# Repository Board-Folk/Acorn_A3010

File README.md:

# Reproduction A3010 PCB #

This repository contains the schematics and PCB layout for a reproduction
of the Acorn A3010 computer PCB - specifically the 194,003 issue 1.

Other variations of the board exist and may be included as separate designs
at a future date.

Where possible the board matches the location of components and routing of
traces.

## Progress ##

The schematics and PCB design are both complete. An initial fabrication run has
been completed and in the process of being tested. The first board is populated
and while it appears to be working over the post port, there is no apparent video
output

### Changes from first test build ###

The AC inputs to the Mean Well psu were reversed. This should not technically
Be a problem for the psi so can be considered cosmetic.

Footprint pad sizes have been enlarged for the LQFP and J-leg components to aid
With hand assembly.

### Known issues ###

The specified fuse rating for the AC input is inadequate for the Mean Well psu.
The initial power-up produces a spike in current that blows the fuse immediately,
it may prove more appropriate to remove the fuse and add protection to the outputs 

## Factory Fixes ##

The original boards include a number of fixes, these have been incorporated
into the design where possible.

## Variations From Standard ##

In a few places the board is non-standard to allow the use of modern, available
components, most notably the power supply area of the board. Instead of the 
original circuits the board is designed to accept a Mean Well unit that is 
both lighter and more efficient.

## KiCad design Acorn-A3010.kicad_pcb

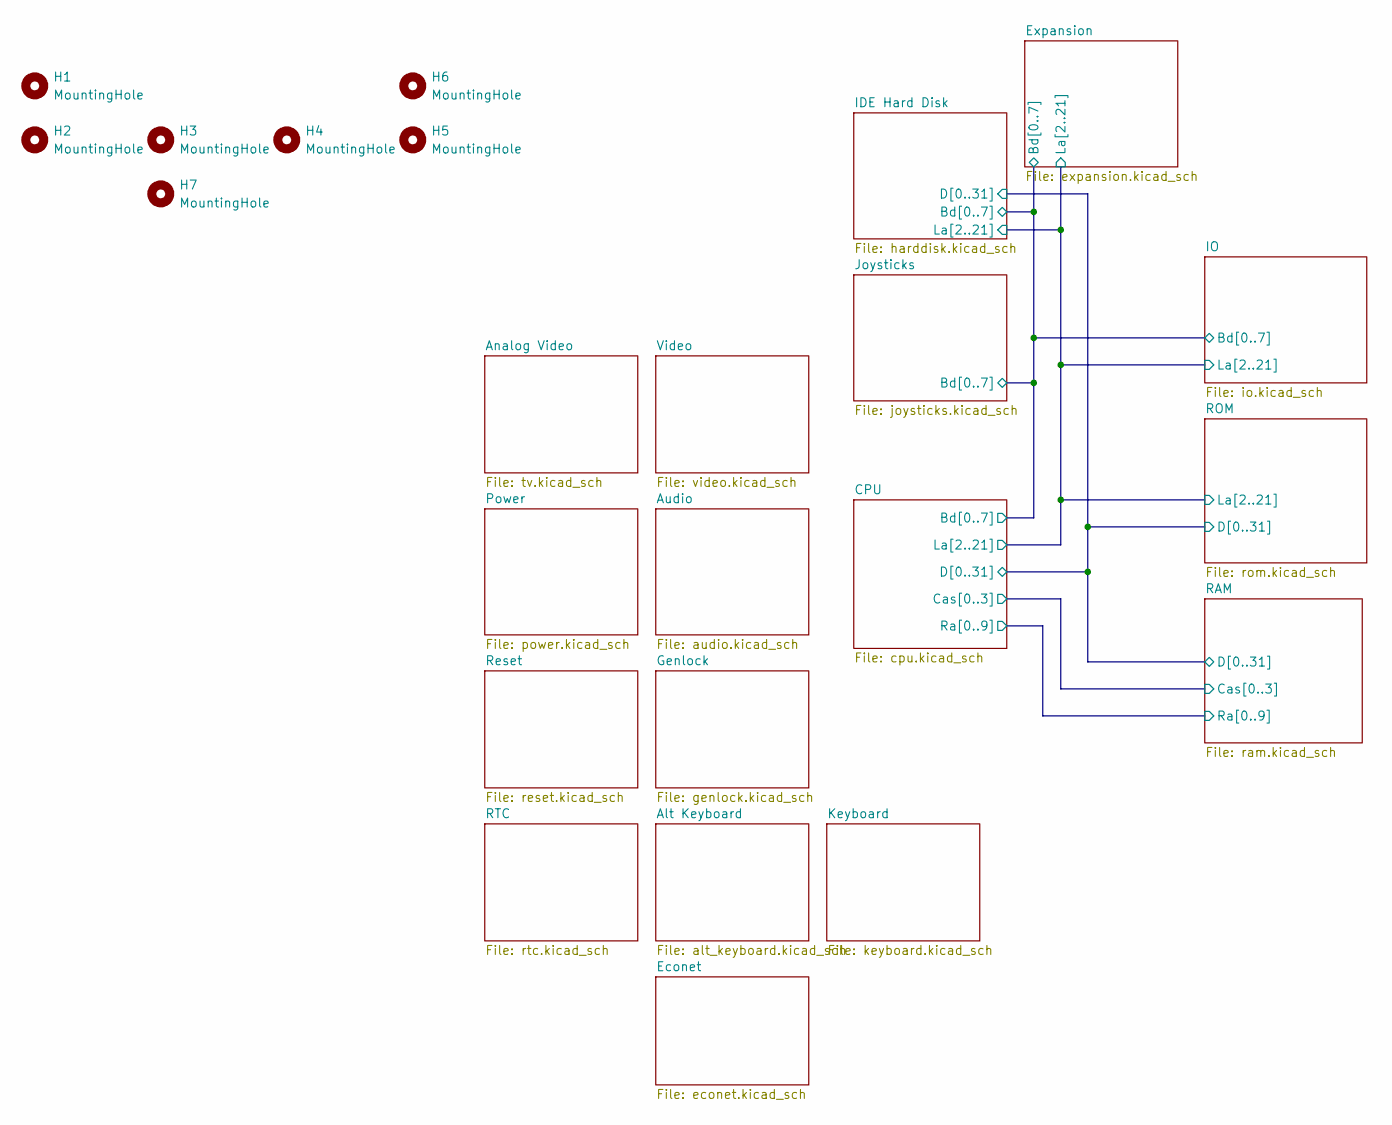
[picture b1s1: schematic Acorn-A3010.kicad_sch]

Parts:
H1, H2, H3, H4, H5, H6, H7: MountingHole; MountingHole_3.2mm_M3

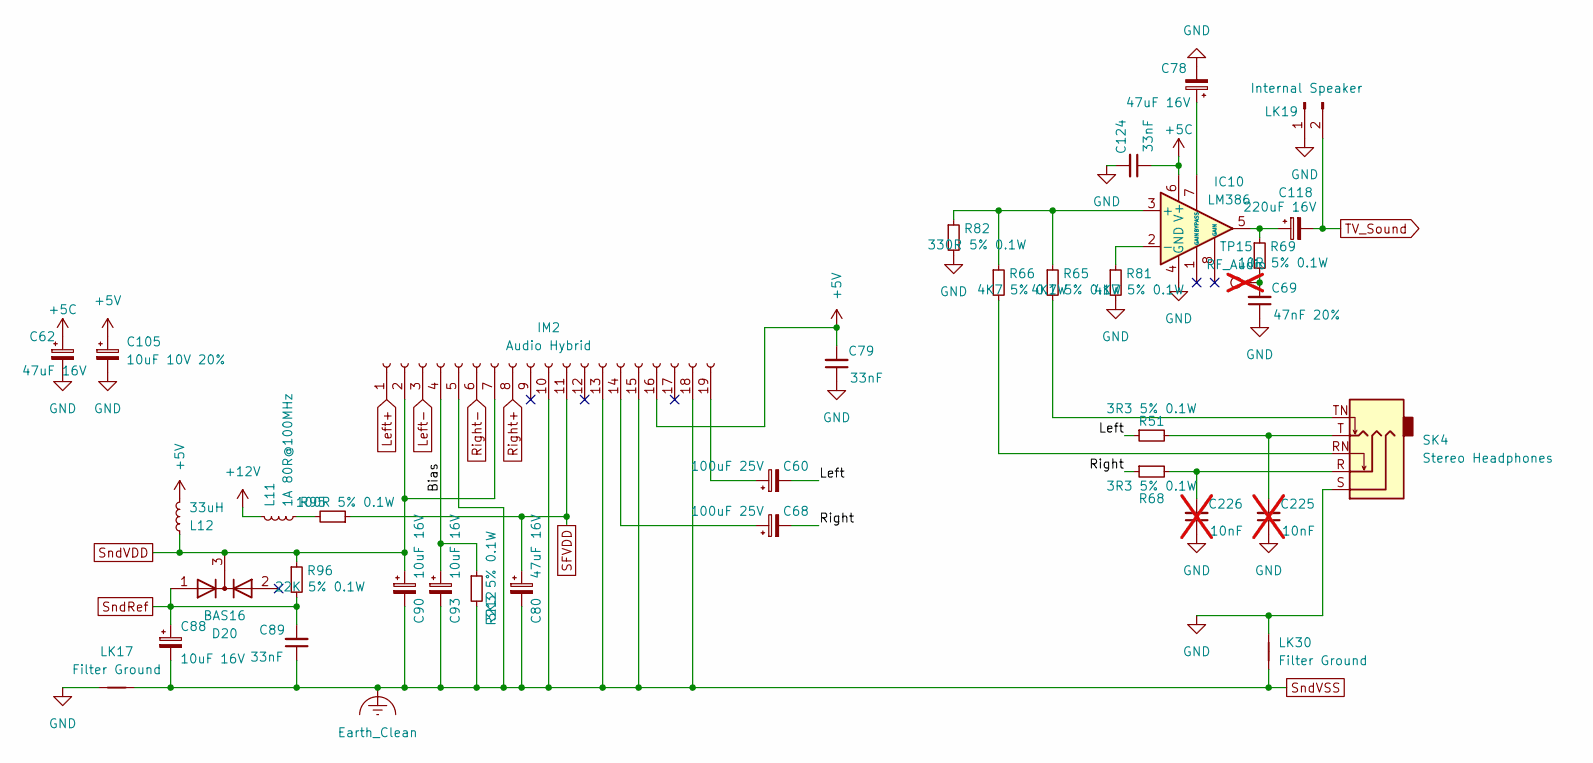
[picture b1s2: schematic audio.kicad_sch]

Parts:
C60, C68: 100uF 25V; CP_Radial_D8.0mm_P5.00mm
C62, C78, C80: 47uF 16V; CP_Radial_D8.0mm_P5.00mm
C69: 47nF 20%; C_0805_2012Metric; LCSC C107154
C79, C89, C124: 33nF; C_0805_2012Metric; LCSC C344201
C88, C90, C93: 10uF 16V; CP_Radial_Tantal_D4.5mm_P5.00mm
C105: 10uF 10V 20%; CP_Radial_Tantal_D7.0mm_P5.00mm
C118: 220uF 16V; CP_Radial_D8.0mm_P5.00mm
C225, C226: 10nF; C_0805_2012Metric; LCSC C83170; not fitted
D20: BAS16; SOT-23-3
IC10: LM386; SOIC-8_3.9x4.9mm_P1.27mm; LCSC C201575
IM2: Audio Hybrid; Audio_Hybrid
L11: 1A 80R@100MHz; L_Acorn_8x3mm
L12: 33uH; L_Axial_L7.0mm_D3.3mm_P12.70mm_Horizontal_Fastron_MICC
LK17, LK30: Filter Ground; Link_Connected
LK19: Internal Speaker; PinHeader_1x02_P2.54mm_Vertical
R51, R68: 3R3 5% 0.1W; R_0805_2012Metric; LCSC C2907250
R65, R66, R81: 4K7 5% 0.1W; R_0805_2012Metric; LCSC C2907326
R69: 10R 5% 0.1W; R_0805_2012Metric; LCSC C96347
R82: 330R 5% 0.1W; R_0805_2012Metric; LCSC C17630
R95: 100R 5% 0.1W; R_0805_2012Metric; LCSC C17408
R96: 22K 5% 0.1W; R_0805_2012Metric; LCSC C17560
R212: 3K3 5% 0.1W; R_0805_2012Metric; LCSC C2930266
SK4: Stereo Headphones; Jack_3.5mm_CUI_SJ1-3525N_Horizontal
TP15: RF_Audio; TestPoint_Pad_D1.0mm; not fitted

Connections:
+5C: C62.1, C124.1, IC10.6 (V+); also elsewhere on the board
+5V: C79.2, C105.1, IM2.16, L12.2; also elsewhere on the board
+12V: L11.1; also elsewhere on the board
/Audio/Bias: C93.1, IM2.4, R212.1
/Audio/Left: C60.2, R51.1
/Audio/Right: C68.2, R68.1
GND: C62.2, C69.1, C78.2, C79.1, C105.2, C124.2, C225.1, C226.1, IC10.4 (GND), LK17.1, LK19.1, LK30.2, R81.2, R82.2, SK4.S; also elsewhere on the board
Left+: IM2.1; also elsewhere on the board
Left-: IM2.3; also elsewhere on the board
unnamed: C69.2, R69.2, TP15.1
unnamed: C118.1, IC10.5, R69.1
unnamed: C225.2, R51.2, SK4.T
unnamed: C226.2, R68.2, SK4.R
unnamed: IC10.3 (+), R65.1, R66.1, R82.1
unnamed: IC10.2 (-), R81.1
unnamed: C78.1, IC10.7 (BYPASS)
unnamed: C68.1, IM2.14
unnamed: C60.1, IM2.19
unnamed: L11.2, R95.2
unnamed: R65.2, SK4.TN
unnamed: R66.2, SK4.RN
Right+: IM2.8; also elsewhere on the board
Right-: IM2.6; also elsewhere on the board
SFVDD: C80.1, IM2.11, R95.1
SndRef: C88.1, C89.2, D20.1 (A), R96.2; also elsewhere on the board
SndVDD: C90.1, D20.3 (K), IM2.2, IM2.7, L12.1, R96.1; also elsewhere on the board
SndVSS: C80.2, C88.2, C89.1, C90.2, C93.2, IM2.5, IM2.10, IM2.13, IM2.15, IM2.18, LK17.2, LK30.1, R212.2; also elsewhere on the board
TV_Sound: C118.2, LK19.2; also elsewhere on the board

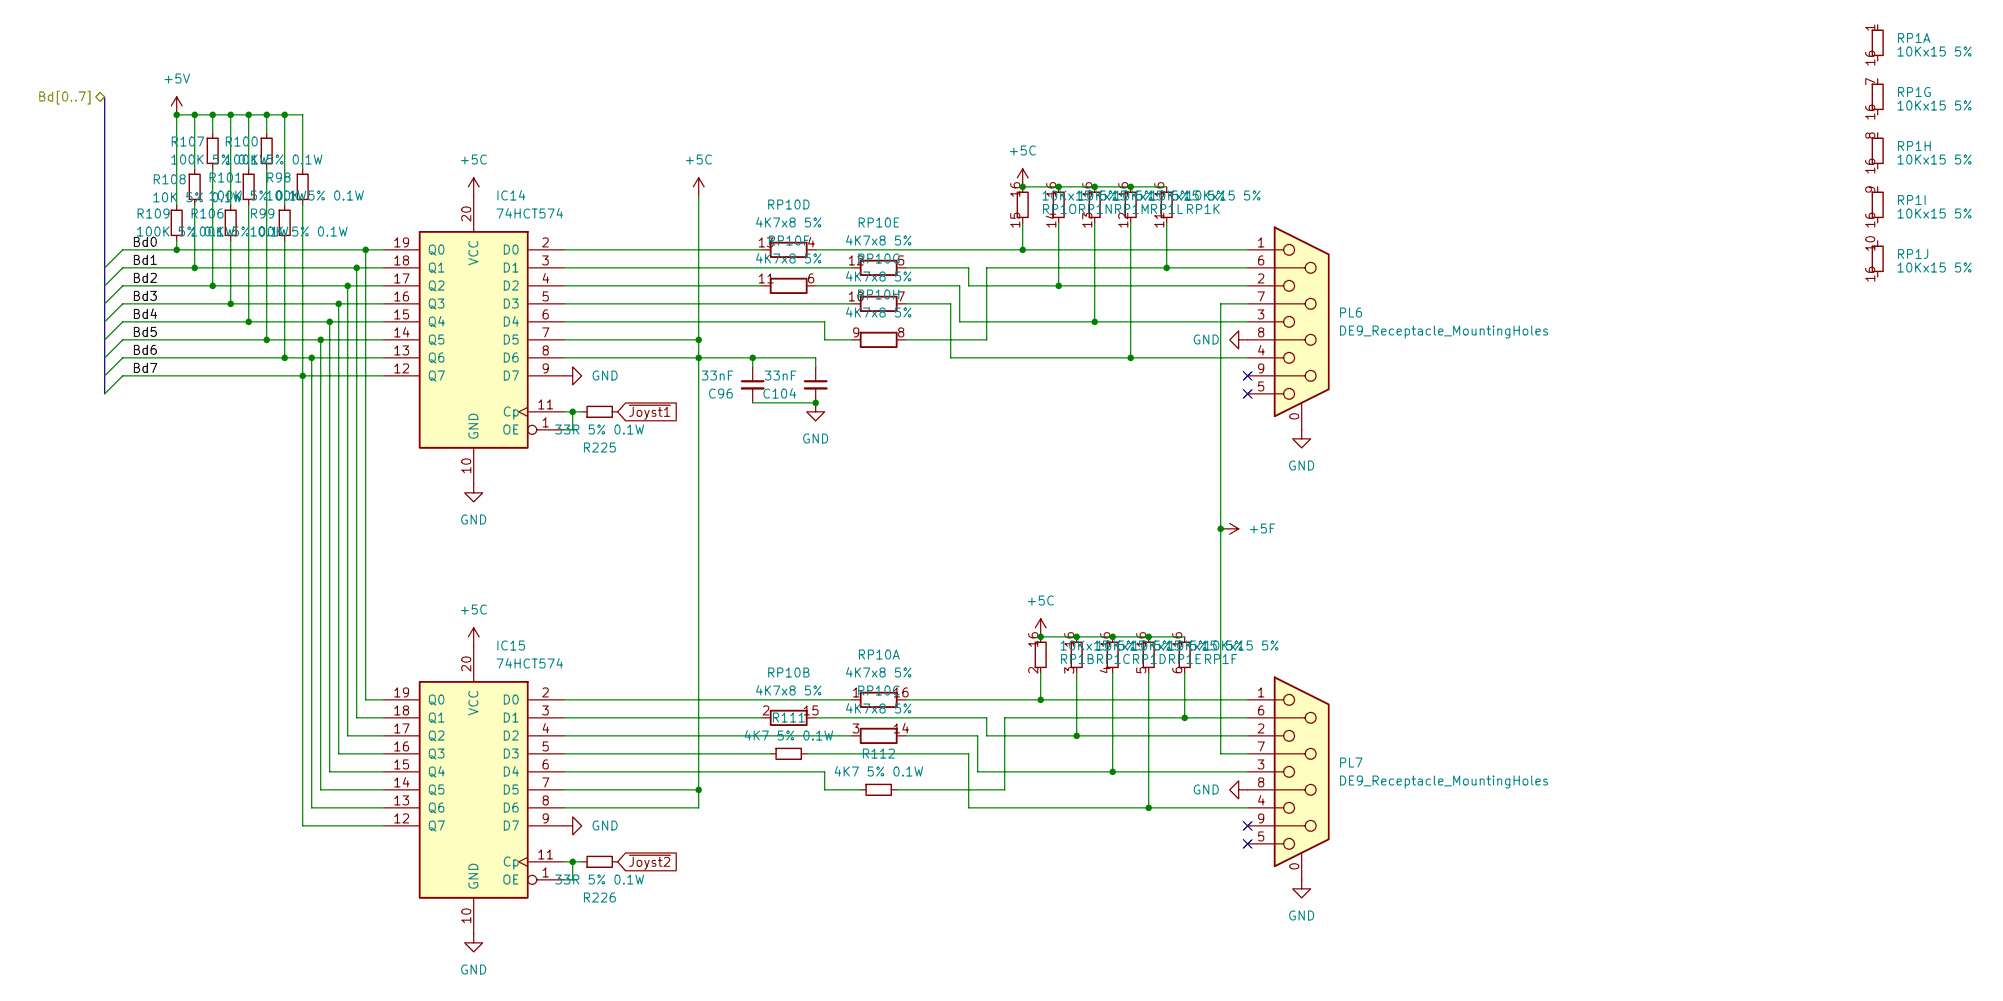
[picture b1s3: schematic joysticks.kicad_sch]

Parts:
C96, C104: 33nF; C_0805_2012Metric; LCSC C344201
IC14, IC15: 74HCT574; SOIC-20W_7.5x12.8mm_P1.27mm; LCSC C6001
PL6, PL7: DE9_Receptacle_MountingHoles; DSUB-9_Male_Horizontal_P2.77x2.84mm_EdgePinOffset9.90mm_Hou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
R98, R99, R100, R101, R106, R107, R109: 100K 5% 0.1W; R_0805_2012Metric; LCSC C149504
R108: 10K 5% 0.1W; R_0805_2012Metric; LCSC C2907219
R111, R112: 4K7 5% 0.1W; R_0805_2012Metric; LCSC C2907326
R225, R226: 33R 5% 0.1W; R_0805_2012Metric; LCSC C17630
RP1: 10Kx15 5%; SOIC-16W_5.3x10.2mm_P1.27mm; LCSC C1738939
RP10: 4K7x8 5%; SOIC-16W_5.3x10.2mm_P1.27mm; LCSC C1739872

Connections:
+5C: C96.1, C104.1, IC14.7 (D5), IC14.8 (D6), IC14.20 (VCC), IC15.7 (D5), IC15.8 (D6), IC15.20 (VCC), RP1.16; also elsewhere on the board
+5F: PL6.7, PL7.7; also elsewhere on the board
+5V: R98.1, R99.1, R100.1, R101.1, R106.1, R107.1, R108.1, R109.1; also elsewhere on the board
/CPU/Bd0: IC14.19 (Q0), IC15.19 (Q0), R109.2; also elsewhere on the board
/CPU/Bd1: IC14.18 (Q1), IC15.18 (Q1), R108.2; also elsewhere on the board
/CPU/Bd2: IC14.17 (Q2), IC15.17 (Q2), R107.2; also elsewhere on the board
/CPU/Bd3: IC14.16 (Q3), IC15.16 (Q3), R106.2; also elsewhere on the board
/CPU/Bd4: IC14.15 (Q4), IC15.15 (Q4), R101.2; also elsewhere on the board
/CPU/Bd5: IC14.14 (Q5), IC15.14 (Q5), R100.2; also elsewhere on the board
/CPU/Bd6: IC14.13 (Q6), IC15.13 (Q6), R99.2; also elsewhere on the board
/CPU/Bd7: IC14.12 (Q7), IC15.12 (Q7), R98.2; also elsewhere on the board
GND: C96.2, C104.2, IC14.9 (D7), IC14.10 (GND), IC15.9 (D7), IC15.10 (GND), PL6.0 (PAD), PL6.8, PL7.0 (PAD), PL7.8; also elsewhere on the board
unnamed: IC14.1 (OE), IC14.11 (Cp), R225.1
unnamed: IC14.2 (D0), RP10.13 (R4.2)
unnamed: IC14.3 (D1), RP10.12 (R5.2)
unnamed: IC14.4 (D2), RP10.11 (R6.2)
unnamed: IC14.5 (D3), RP10.10 (R7.2)
unnamed: IC14.6 (D4), RP10.9 (R8.2)
unnamed: IC15.1 (OE), IC15.11 (Cp), R226.1
unnamed: IC15.2 (D0), RP10.1 (R1.1)
unnamed: IC15.3 (D1), RP10.2 (R2.1)
unnamed: IC15.4 (D2), RP10.3 (R3.1)
unnamed: IC15.5 (D3), R111.1
unnamed: IC15.6 (D4), R112.1
unnamed: PL7.4, R111.2, RP1.5
unnamed: PL7.6, R112.2, RP1.6
unnamed: PL7.1, RP1.2, RP10.16 (R1.2)
unnamed: PL7.2, RP1.3, RP10.15 (R2.2)
unnamed: PL7.3, RP1.4, RP10.14 (R3.2)
unnamed: PL6.1, RP1.15, RP10.4 (R4.1)
unnamed: PL6.2, RP1.14, RP10.5 (R5.1)
unnamed: PL6.3, RP1.13, RP10.6 (R6.1)
unnamed: PL6.4, RP1.12, RP10.7 (R7.1)
unnamed: PL6.6, RP1.11, RP10.8 (R8.1)
~Joyst1: R225.2; also elsewhere on the board
~Joyst2: R226.2; also elsewhere on the board

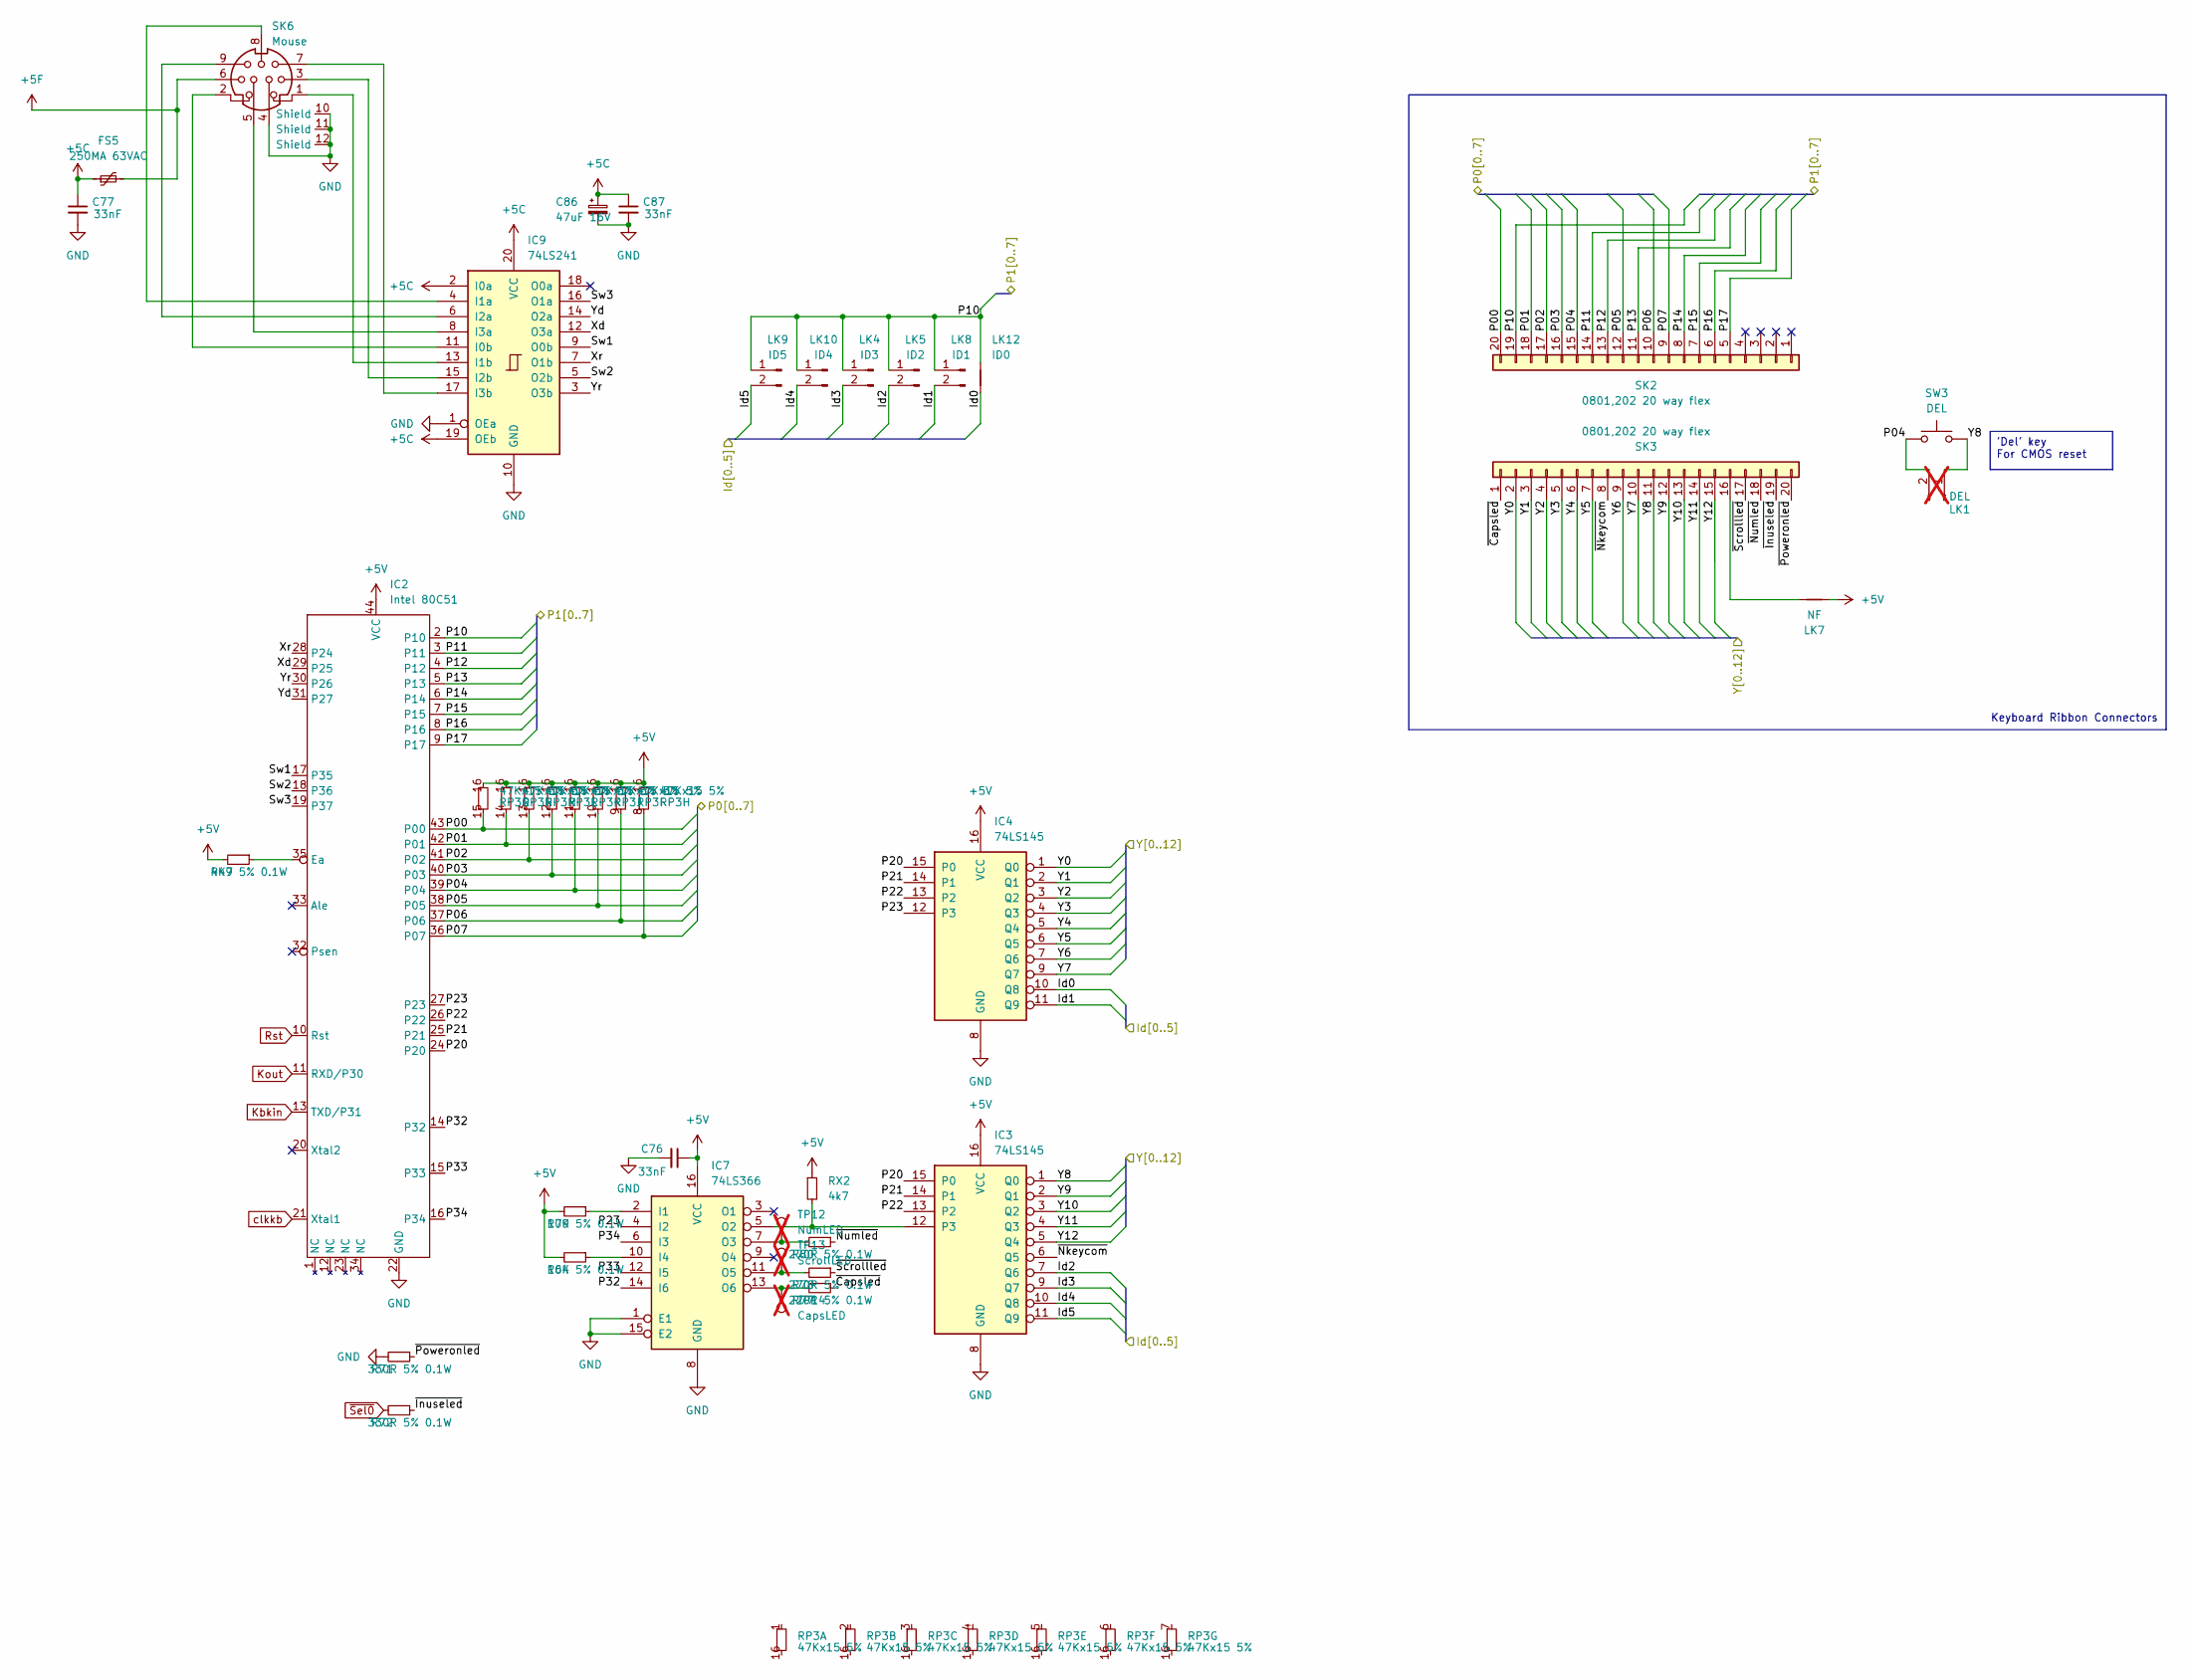
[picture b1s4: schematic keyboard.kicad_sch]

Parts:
C76, C77, C87: 33nF; C_0805_2012Metric; LCSC C344201
C86: 47uF 16V; CP_Radial_D8.0mm_P5.00mm
FS5: 250MA 63VAC; Fuse_2512_6332Metric_Pad1.52x3.35mm_HandSolder
IC2: Intel 80C51; PLCC-44
IC3, IC4: 74LS145; SOIC-16_3.9x9.9mm_P1.27mm; LCSC C60829
IC7: 74LS366; SOIC-16_3.9x9.9mm_P1.27mm
IC9: 74LS241; SOIC-20W_7.5x12.8mm_P1.27mm; LCSC C2676097
LK1: DEL; Link; not fitted
LK4: ID3; Link
LK5: ID2; Link
LK7: NF; Link_Connected
LK8: ID1; Link
LK9: ID5; Link
LK10: ID4; Link
LK12: ID0; Link_Connected
R49: 4K7 5% 0.1W; R_0805_2012Metric; LCSC C2907326
R64, R79: 10K 5% 0.1W; R_0805_2012Metric; LCSC C2907219
R71, R72: 330R 5% 0.1W; R_0805_2012Metric; LCSC C17630
R77: 220R 5% 0.1W; R_0805_2012Metric; LCSC C17557
R78, R80: 270R 5% 0.1W; R_0805_2012Metric; LCSC C17590
RP3: 47Kx15 5%; SOIC-16W_5.3x10.2mm_P1.27mm; LCSC C1739866
RX2: 4k7; R_Axial_DIN0204_L3.6mm_D1.6mm_P7.62mm_Horizontal
SK2, SK3: 0801,202 20 way flex; PinHeader_1x20_P2.54mm_Vertical
SK6: Mouse; Mini-DIN_9
SW3: DEL; SW_SPST_TS-1088-xR020; LCSC C720477
TP12: NumLED; TestPoint_Pad_D1.0mm; not fitted
TP13: ScrollLED; TestPoint_Pad_D1.0mm; not fitted
TP14: CapsLED; TestPoint_Pad_D1.0mm; not fitted

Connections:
+5C: C77.1, C86.1, C87.1, FS5.1, IC9.2 (I0a), IC9.19 (OEb), IC9.20 (VCC); also elsewhere on the board
+5F: FS5.2, SK6.6; also elsewhere on the board
+5V: C76.1, IC2.44 (VCC), IC3.16 (VCC), IC4.16 (VCC), IC7.16 (VCC), LK7.1, R49.2, R64.2, R79.2, RP3.16, RX2.1; also elsewhere on the board
/Keyboard/Id0: IC4.10 (Q8), LK12.2
/Keyboard/Id1: IC4.11 (Q9), LK8.2
/Keyboard/Id2: IC3.7 (Q6), LK5.2
/Keyboard/Id3: IC3.9 (Q7), LK4.2
/Keyboard/Id4: IC3.10 (Q8), LK10.2
/Keyboard/Id5: IC3.11 (Q9), LK9.2
/Keyboard/P00: IC2.43 (P00), RP3.15, SK2.20
/Keyboard/P01: IC2.42 (P01), RP3.14, SK2.18
/Keyboard/P02: IC2.41 (P02), RP3.13, SK2.17
/Keyboard/P03: IC2.40 (P03), RP3.12, SK2.16
/Keyboard/P04: IC2.39 (P04), LK1.2, RP3.11, SK2.15, SW3.1
/Keyboard/P05: IC2.38 (P05), RP3.10, SK2.12
/Keyboard/P06: IC2.37 (P06), RP3.9, SK2.10
/Keyboard/P07: IC2.36 (P07), RP3.8, SK2.9
/Keyboard/P10: IC2.2 (P10), LK4.1, LK5.1, LK8.1, LK9.1, LK10.1, LK12.1, SK2.19
/Keyboard/P11: IC2.3 (P11), SK2.14
/Keyboard/P12: IC2.4 (P12), SK2.13
/Keyboard/P13: IC2.5 (P13), SK2.11
/Keyboard/P14: IC2.6 (P14), SK2.8
/Keyboard/P15: IC2.7 (P15), SK2.7
/Keyboard/P16: IC2.8 (P16), SK2.6
/Keyboard/P17: IC2.9 (P17), SK2.5
/Keyboard/P20: IC2.24 (P20), IC3.15 (P0), IC4.15 (P0)
/Keyboard/P21: IC2.25 (P21), IC3.14 (P1), IC4.14 (P1)
/Keyboard/P22: IC2.26 (P22), IC3.13 (P2), IC4.13 (P2)
/Keyboard/P23: IC2.27 (P23), IC4.12 (P3), IC7.4 (I2)
/Keyboard/P32: IC2.14 (P32), IC7.14 (I6)
/Keyboard/P33: IC2.15 (P33), IC7.12 (I5)
/Keyboard/P34: IC2.16 (P34), IC7.6 (I3)
/Keyboard/Sw1: IC2.17 (P35), IC9.9 (O0b)
/Keyboard/Sw2: IC2.18 (P36), IC9.5 (O2b)
/Keyboard/Sw3: IC2.19 (P37), IC9.16 (O1a)
/Keyboard/Xd: IC2.29 (P25), IC9.12 (O3a)
/Keyboard/Xr: IC2.28 (P24), IC9.7 (O1b)
/Keyboard/Y0: IC4.1 (Q0), SK3.2
/Keyboard/Y1: IC4.2 (Q1), SK3.3
/Keyboard/Y2: IC4.3 (Q2), SK3.4
/Keyboard/Y3: IC4.4 (Q3), SK3.5
/Keyboard/Y4: IC4.5 (Q4), SK3.6
/Keyboard/Y5: IC4.6 (Q5), SK3.7
/Keyboard/Y6: IC4.7 (Q6), SK3.9
/Keyboard/Y7: IC4.9 (Q7), SK3.10
/Keyboard/Y8: IC3.1 (Q0), LK1.1, SK3.11, SW3.2
/Keyboard/Y9: IC3.2 (Q1), SK3.12
/Keyboard/Y10: IC3.3 (Q2), SK3.13
/Keyboard/Y11: IC3.4 (Q3), SK3.14
/Keyboard/Y12: IC3.5 (Q4), SK3.15
/Keyboard/Yd: IC2.31 (P27), IC9.14 (O2a)
/Keyboard/Yr: IC2.30 (P26), IC9.3 (O3b)
/Keyboard/~Capsled: R77.1, SK3.1
/Keyboard/~Inuseled: R72.1, SK3.19
/Keyboard/~Nkeycom: IC3.6 (Q5), SK3.8
/Keyboard/~Numled: R80.1, SK3.18
/Keyboard/~Poweronled: R71.1, SK3.20
/Keyboard/~Scrollled: R78.1, SK3.17
GND: C76.2, C77.2, C86.2, C87.2, IC2.22 (GND), IC3.8 (GND), IC4.8 (GND), IC7.1 (E1), IC7.8 (GND), IC7.15 (E2), IC9.1 (OEa), IC9.10 (GND), R71.2, SK6.4, SK6.10 (Shield), SK6.11 (Shield), SK6.12 (Shield); also elsewhere on the board
Kbkin: IC2.13 (TXD/P31); also elsewhere on the board
Kout: IC2.11 (RXD/P30); also elsewhere on the board
unnamed: IC2.35 (Ea), R49.1
unnamed: IC3.12 (P3), IC7.5 (O2), RX2.2
unnamed: IC7.2 (I1), R79.1
unnamed: IC7.10 (I4), R64.1
unnamed: IC7.7 (O3), R80.2, TP12.1
unnamed: IC7.11 (O5), R78.2, TP13.1
unnamed: IC7.13 (O6), R77.2, TP14.1
unnamed: IC9.11 (I0b), SK6.2
unnamed: IC9.4 (I1a), SK6.8
unnamed: IC9.13 (I1b), SK6.1
unnamed: IC9.6 (I2a), SK6.9
unnamed: IC9.15 (I2b), SK6.3
unnamed: IC9.8 (I3a), SK6.5
unnamed: IC9.17 (I3b), SK6.7
unnamed: LK7.2, SK3.16
Rst: IC2.10 (Rst); also elsewhere on the board
clkkb: IC2.21 (Xtal1); also elsewhere on the board
~Sel0: R72.2; also elsewhere on the board

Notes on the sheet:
Keyboard Ribbon Connectors
'Del' key For CMOS reset

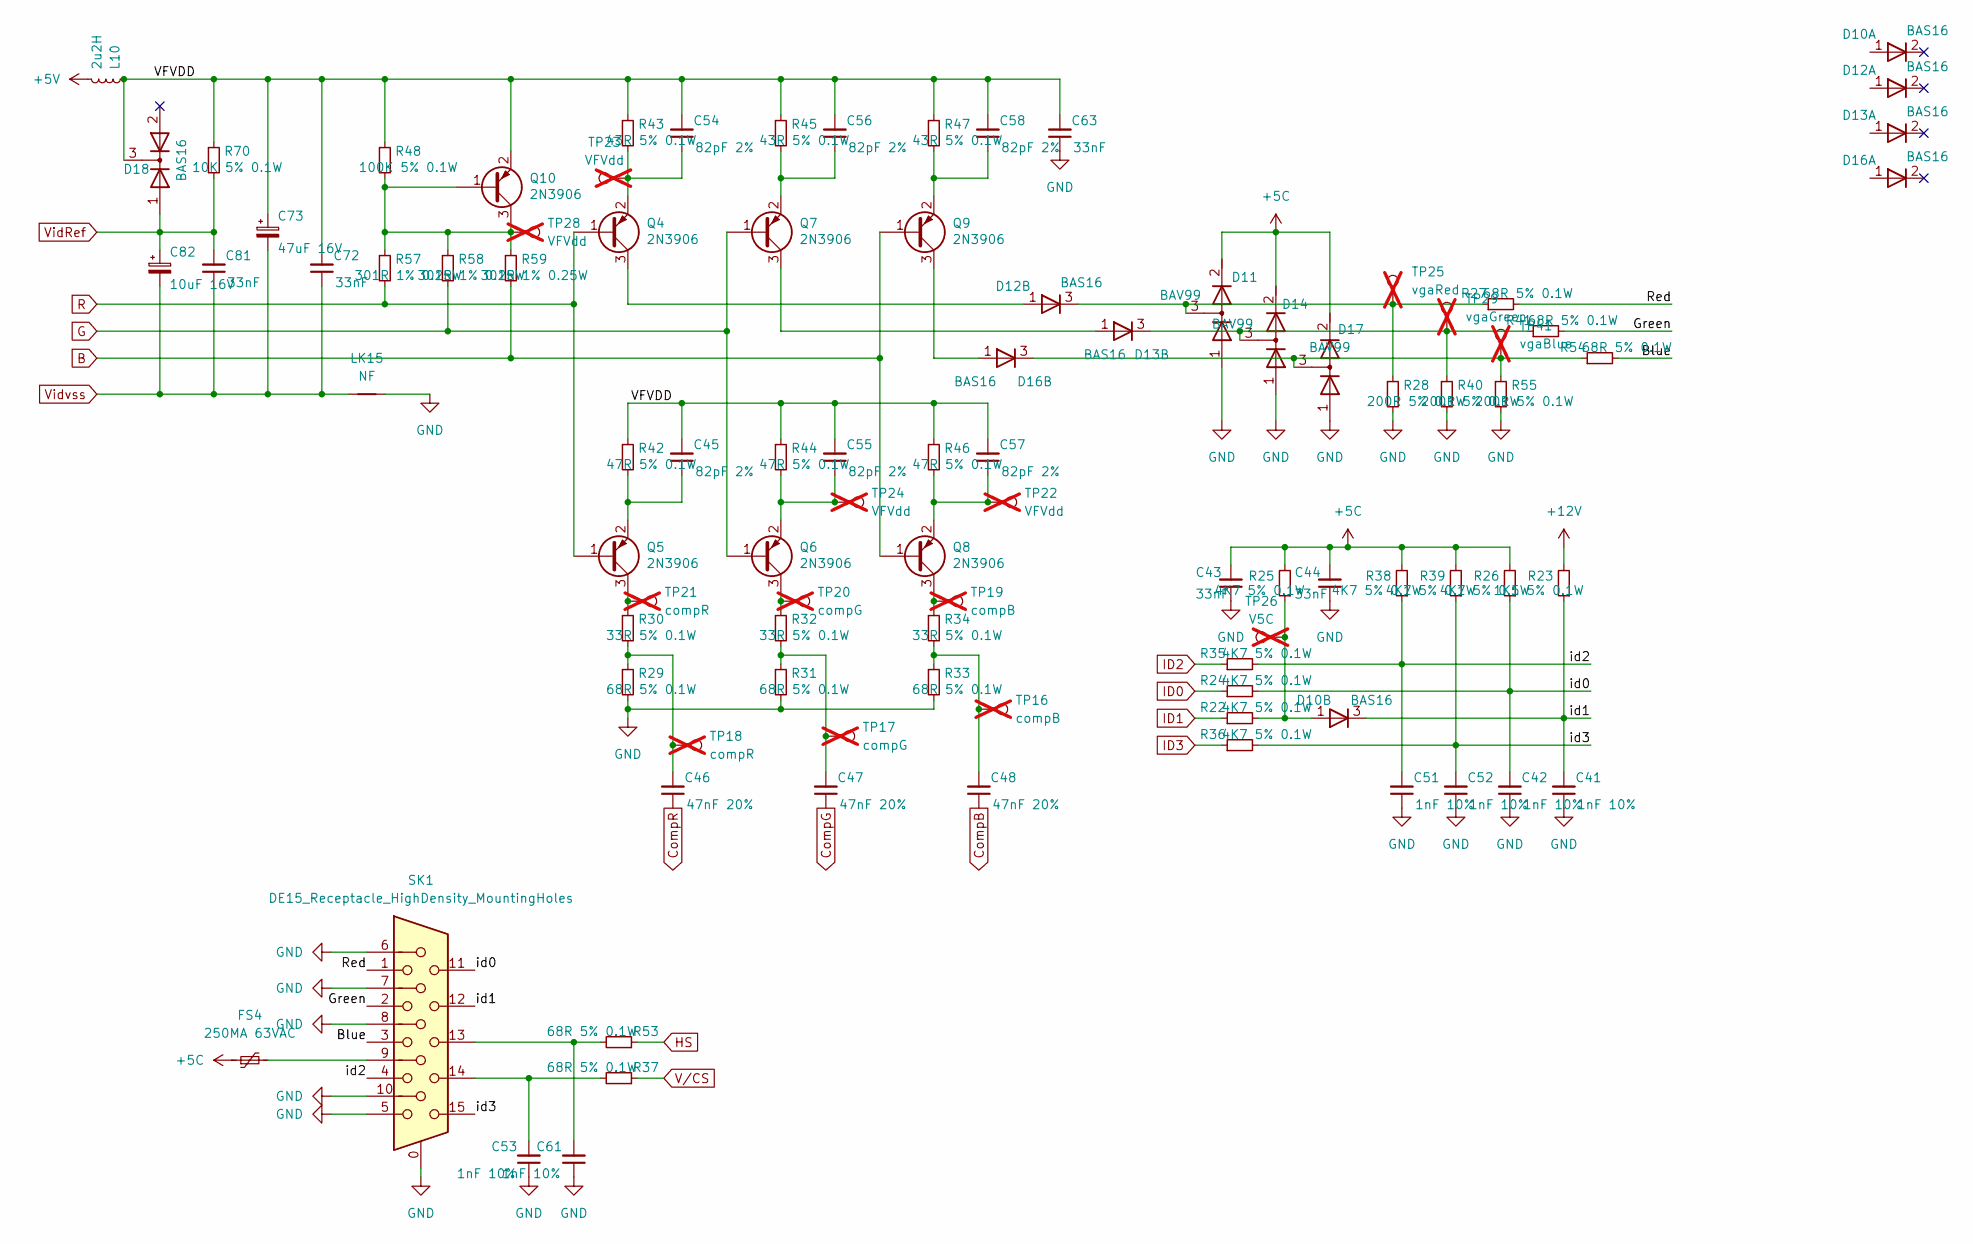
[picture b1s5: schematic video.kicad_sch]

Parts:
C41, C42, C51, C52, C53, C61: 1nF 10%; C_0805_2012Metric; LCSC C46653
C43, C44, C63, C72, C81: 33nF; C_0805_2012Metric; LCSC C344201
C45, C54, C55, C56, C57, C58: 82pF 2%; C_0805_2012Metric; LCSC C113833
C46, C47, C48: 47nF 20%; C_0805_2012Metric; LCSC C107154
C73: 47uF 16V; CP_Radial_D8.0mm_P5.00mm
C82: 10uF 16V; CP_Radial_Tantal_D4.5mm_P5.00mm
D10, D12, D13, D16, D18: BAS16; SOT-23-3
D11, D14, D17: BAV99; SOT-23-3
FS4: 250MA 63VAC; Fuse_2512_6332Metric_Pad1.52x3.35mm_HandSolder
L10: 2u2H; L_Axial_L6.6mm_D2.7mm_P10.16mm_Horizontal_Vishay_IM-2
LK15: NF; Link_Connected
Q4, Q5, Q6, Q7, Q8, Q9, Q10: 2N3906; SOT-23-3; LCSC C49023424
R22, R24, R25, R26, R35, R36, R38, R39: 4K7 5% 0.1W; R_0805_2012Metric; LCSC C2907326
R23: 1K5 5% 0.1W; R_0805_2012Metric; LCSC C2907216
R27, R29, R31, R33, R37, R41, R53, R54: 68R 5% 0.1W; R_0805_2012Metric; LCSC C137498
R28, R40, R55: 200R 5% 0.1W; R_0805_2012Metric; LCSC C17540
R30, R32, R34: 33R 5% 0.1W; R_0805_2012Metric; LCSC C17634
R42, R44: 47R 5% 0.1W; R_0805_2012Metric; LCSC C4368
R43, R45, R47: 43R 5% 0.1W; R_0805_2012Metric; LCSC C4368
R46: 47R 5% 0.1W; R_0805_2012Metric; LCSC C2907268
R48: 100K 5% 0.1W; R_0805_2012Metric; LCSC C149504
R57, R58, R59: 301R 1% 0.25W; R_1206_3216Metric; LCSC C2483588
R70: 10K 5% 0.1W; R_0805_2012Metric; LCSC C2907219
SK1: DE15_Receptacle_HighDensity_MountingHoles; DSUB-15-HD_Socket_Horizontal_P2.29x2.54mm_EdgePinOffset8.35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
TP16, TP19: compB; TestPoint_Pad_D1.0mm; not fitted
TP17, TP20: compG; TestPoint_Pad_D1.0mm; not fitted
TP18, TP21: compR; TestPoint_Pad_D1.0mm; not fitted
TP22, TP23, TP24, TP28: VFVdd; TestPoint_Pad_D1.0mm; not fitted
TP25: vgaRed; TestPoint_Pad_D1.0mm; not fitted
TP26: V5C; TestPoint_Pad_D1.0mm; not fitted
TP29: vgaGreen; TestPoint_Pad_D1.0mm; not fitted
TP41: vgaBlue; TestPoint_Pad_D1.0mm; not fitted

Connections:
+5C: C43.2, C44.2, D11.2 (K), D14.2 (K), D17.2 (K), FS4.1, R25.2, R26.2, R38.2, R39.2; also elsewhere on the board
+5V: L10.2; also elsewhere on the board
+12V: R23.2; also elsewhere on the board
/Video/Blue: R54.2, SK1.3
/Video/Green: R41.2, SK1.2
/Video/Red: R27.2, SK1.1
/Video/VFVDD: C45.2, C54.2, C55.2, C56.2, C57.2, C58.2, C63.2, C72.2, C73.1, D18.3 (K), L10.1, Q10.2 (E), R42.1, R43.1, R44.1, R45.1, R46.1, R47.1, R48.1, R70.1
/Video/id0: C42.2, R24.2, R26.1, SK1.11
/Video/id1: C41.2, D10.3 (K), R23.1, SK1.12
/Video/id2: C51.2, R35.2, R38.1, SK1.4
/Video/id3: C52.2, R36.2, R39.1, SK1.15
B: Q8.1 (B), Q9.1 (B), R59.2; also elsewhere on the board
CompB: C48.1; also elsewhere on the board
CompG: C47.1; also elsewhere on the board
CompR: C46.1; also elsewhere on the board
G: Q6.1 (B), Q7.1 (B), R58.2; also elsewhere on the board
GND: C41.1, C42.1, C43.1, C44.1, C51.1, C52.1, C53.1, C61.1, C63.1, D11.1 (A), D14.1 (A), D17.1 (A), LK15.2, R28.2, R29.2, R31.2, R33.2, R40.2, R55.2, SK1.0, SK1.5, SK1.6, SK1.7, SK1.8, SK1.10; also elsewhere on the board
HS: R53.1; also elsewhere on the board
ID0: R24.1; also elsewhere on the board
ID1: R22.1; also elsewhere on the board
ID2: R35.1; also elsewhere on the board
ID3: R36.1; also elsewhere on the board
unnamed: C46.2, R29.1, R30.2, TP18.1
unnamed: C47.2, R31.1, R32.2, TP17.1
unnamed: C48.2, R33.1, R34.2, TP16.1
unnamed: C53.2, R37.2, SK1.14
unnamed: C61.2, R53.2, SK1.13
unnamed: D10.1 (A), R22.2, R25.1, TP26.1
unnamed: D11.3 (common), D12.3 (K), R27.1, R28.1, TP25.1
unnamed: D12.1 (A), Q4.3 (C)
unnamed: D13.1 (A), Q7.3 (C)
unnamed: D13.3 (K), D14.3 (common), R40.1, R41.1, TP29.1
unnamed: D16.1 (A), Q9.3 (C)
unnamed: D16.3 (K), D17.3 (common), R54.1, R55.1, TP41.1
unnamed: FS4.2, SK1.9
unnamed: C54.1, Q4.2 (E), R43.2, TP23.1
unnamed: Q5.3 (C), R30.1, TP21.1
unnamed: C45.1, Q5.2 (E), R42.2
unnamed: Q6.3 (C), R32.1, TP20.1
unnamed: C55.1, Q6.2 (E), R44.2, TP24.1
unnamed: C56.1, Q7.2 (E), R45.2
unnamed: Q8.3 (C), R34.1, TP19.1
unnamed: C57.1, Q8.2 (E), R46.2, TP22.1
unnamed: C58.1, Q9.2 (E), R47.2
unnamed: Q10.1 (B), Q10.3 (C), R48.2, R57.1, R58.1, R59.1, TP28.1
R: Q4.1 (B), Q5.1 (B), R57.2; also elsewhere on the board
VidRef: C81.2, C82.1, D18.1 (A), R70.2; also elsewhere on the board
Vidvss: C72.1, C73.2, C81.1, C82.2, LK15.1; also elsewhere on the board
V/CS: R37.1; also elsewhere on the board
